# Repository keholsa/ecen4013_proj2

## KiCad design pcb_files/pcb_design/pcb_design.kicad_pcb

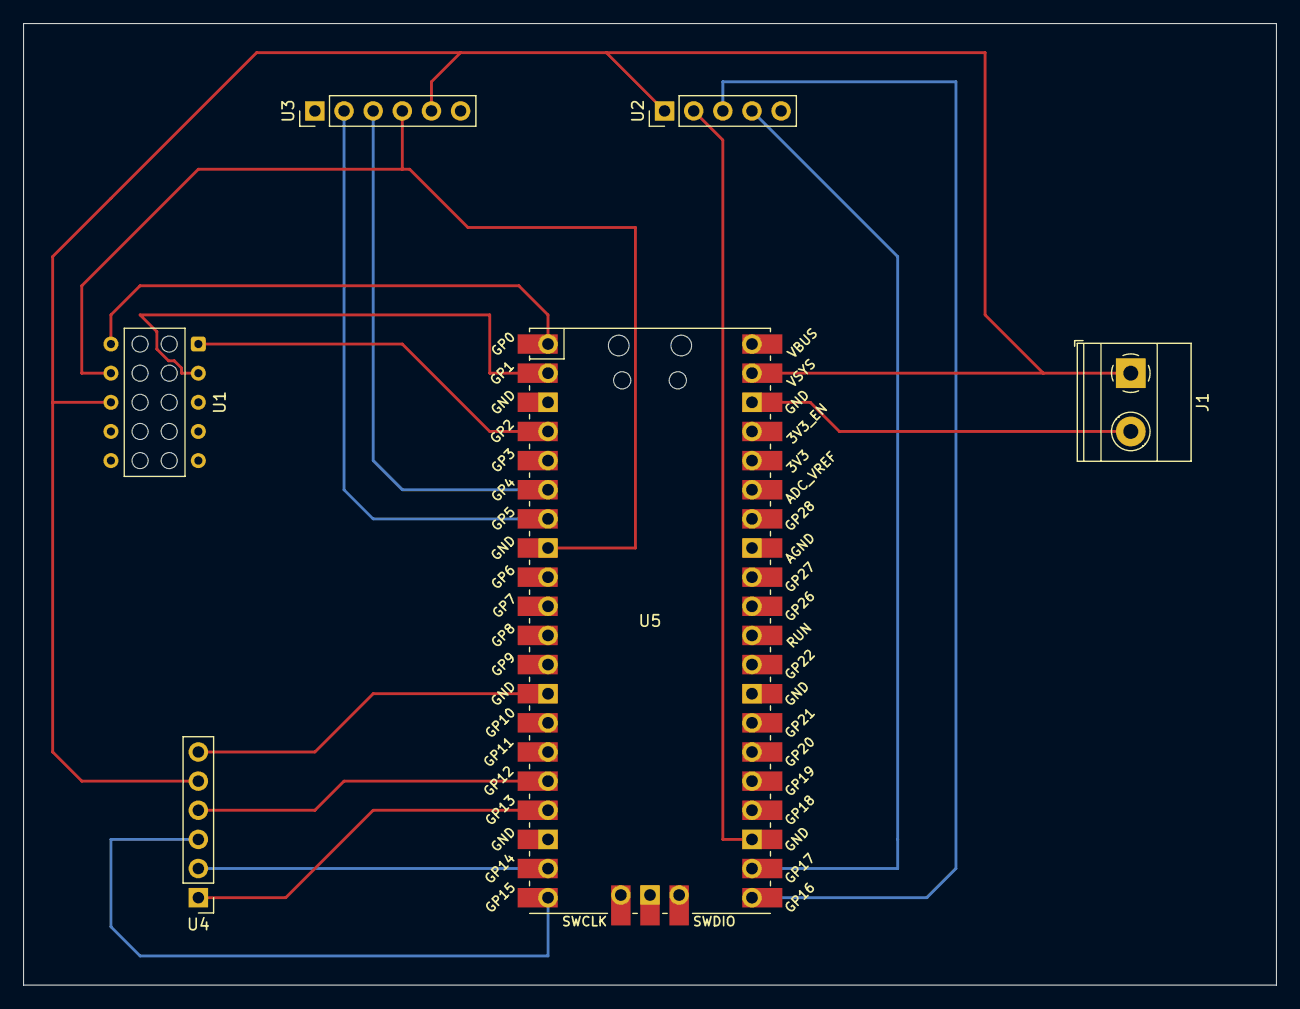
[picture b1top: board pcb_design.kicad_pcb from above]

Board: 2 copper layers, 109.2 x 83.8 mm, 6 parts (0 on the bottom side), 16 nets.

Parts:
J1: Screw_Terminal_01x02; TerminalBlock_Phoenix_MKDS-1,5-2-5.08_1x02_P5.08mm_Horizont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
U1: Samtec_HLE-105-02-xx-DV-PE_2x05_P2.54mm_Horizontal
U2: PinHeader_1x05_P2.54mm_Vertical
U3, U4: PinHeader_1x06_P2.54mm_Vertical
U5: Pico; RPi_Pico_SMD_TH

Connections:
unnamed: J1.1, U1.6 (VIN), U2.1 (VCC), U3.5 (VCC), U4.5 (VCC), U5.39 (VSYS)
unnamed: J1.2, U5.38 (GND)
unnamed: U1.4 (GND), U3.4 (GND), U5.8 (GND)
unnamed: U1.1 (RST), U5.4 (GPIO2)
unnamed: U1.3 (SCL), U5.2 (GPIO1)
unnamed: U1.2 (SDA), U5.1 (GPIO0)
unnamed: U2.2 (GND), U5.23 (GND)
unnamed: U2.3 (RXD), U5.21 (GPIO16)
unnamed: U2.4 (TXD), U5.22 (GPIO17)
unnamed: U3.2 (RXD), U5.7 (GPIO5)
unnamed: U3.3 (TXD), U5.6 (GPIO4)
unnamed: U4.1 (CS), U5.17 (GPIO13)
unnamed: U4.6 (GND), U5.13 (GND)
unnamed: U4.4 (MISO), U5.16 (GPIO12)
unnamed: U4.3 (MOSI), U5.20 (GPIO15)
unnamed: U4.2 (SCK), U5.19 (GPIO14)

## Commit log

2023-04-19 Create Storage
2023-04-19 Rename Storage to Storage.py
2023-04-24 adding clerical files
2023-04-24 adding test codes
2023-04-24 populating test code files
2023-04-24 sdcard module populated
2023-04-25 gps function completed
2023-04-25 updated pcb files
2023-04-25 adding imu function and module files
2023-04-25 Rename README.txt to README.md
2023-04-25 Rename README.md to README.txt
2023-05-02 Rename SDCard2222.md to SDCard2222.py
2023-05-02 Rename SD_Card.md to SD_Card.py
